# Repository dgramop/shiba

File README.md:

# shiba
An arduino-compatible version of "Pluto", a smartwatch with the same form factor as the F91-W

I abandoned this project after finishing the hardware designs, but I learned a lot from working on it. I learned a lot about KiCAD and EDA stuff in general. I also learned that Arduino is slightly overrated. AVR Microcontrollers are not a one-size fits all, and direct driving an LCD with an MCU doesn't make a whole lot of sense. I had initially planned on direct driving the LCD to save space, but because the MCU I selected did not have a real-time clock, I had to use additional space on the board for an RTC chip that could be configured to interrupt the MCU. This means that there's no space left for other sensors and connectors that could be used to add new features to the watch. I had some ideas involving TOTP and a USB connector to make it act as a U2F device, but power and space constraints make a lot of the features I would want not viable. Maybe later on I'll do a project involving a low-power dumb watch, but it probably won't involve AVR

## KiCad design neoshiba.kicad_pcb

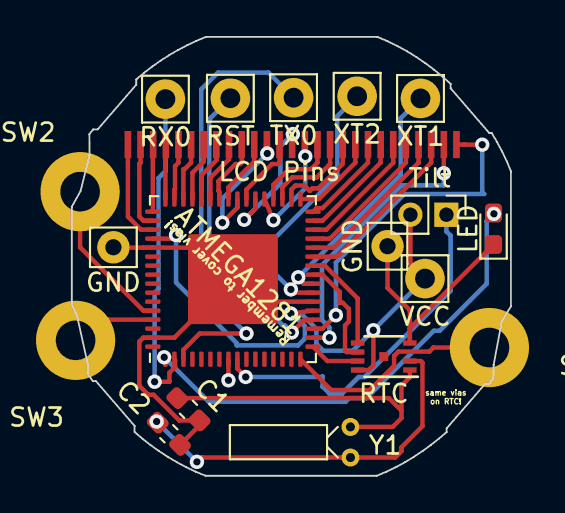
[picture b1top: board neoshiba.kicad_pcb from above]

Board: 2 copper layers, 24.4 x 24.4 mm, 19 parts (0 on the bottom side), 44 nets.

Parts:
ATMEGA1281: ATmega1281V-8MU; QFN-64-1EP_9x9mm_P0.5mm_EP7.65x7.65mm
C1, C2: 15pf; C_0603_1608Metric_Pad1.05x0.95mm_HandSolder
GND: MountingHole_Pad 1.2 or 1mm; Pin_D0.9mm_L10.0mm_W2.4mm_FlatFork
GND#2: MountingHole_Pad, 1.2 or 1mm; Pin_D0.9mm_L10.0mm_W2.4mm_FlatFork
LCD Pins: LCD-F-91W
LED: LED_ALT; LED_0603_1608Metric_Pad1.05x0.95mm_HandSolder
RST: MountingHole_Pad; Pin_D1.1mm_L8.5mm_W2.5mm_FlatFork
RTC: MCP7940N-xSN; DFN-8-1EP_3x2mm_P0.5mm_EP1.3x1.5mm
RX0: MountingHole_Pad; Pin_D1.1mm_L8.5mm_W2.5mm_FlatFork
SW1, SW3: SW_Push; MountingHole_2.2mm_M2_Pad
SW2: SW_Push; MountingHole_2.2mm_M2_Pad-shifted
TX0: MountingHole_Pad; Pin_D1.1mm_L8.5mm_W2.5mm_FlatFork
Tilt: SW_Push; PinHeader_1x02_P2.00mm_Vertical
VCC: MountingHole_Pad; Pin_D1.1mm_L8.5mm_W2.5mm_FlatFork
XT1, XT2: MountingHole_Pad; Pin_D1.1mm_L8.5mm_W2.5mm_FlatFork
Y1: Crystal; Crystal_DS15_D1.5mm_L5.0mm_Horizontal

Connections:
GND: ATMEGA1281.22, ATMEGA1281.53, ATMEGA1281.63, ATMEGA1281.65, C1.1, C2.1, GND.1, GND#2.1, LED.1, RTC.4
unnamed: C1.2, RTC.1, Y1.1
unnamed: C2.2, RTC.2, Y1.2
unnamed: ATMEGA1281.1, LED.2
unnamed: ATMEGA1281.20, RST.1
unnamed: ATMEGA1281.24, XT1.1
unnamed: ATMEGA1281.23, XT2.1
unnamed: ATMEGA1281.2, RX0.1
unnamed: ATMEGA1281.3, TX0.1
unnamed: ATMEGA1281.16, SW1.1
unnamed: ATMEGA1281.60, SW2.1
unnamed: ATMEGA1281.61, SW3.1
unnamed: ATMEGA1281.9, Tilt.1
unnamed: ATMEGA1281.17, RTC.7
unnamed: ATMEGA1281.18, LCD Pins.26
unnamed: ATMEGA1281.19, LCD Pins.27
unnamed: ATMEGA1281.25, RTC.6
unnamed: ATMEGA1281.26, RTC.5
unnamed: ATMEGA1281.27, LCD Pins.25
unnamed: ATMEGA1281.28, LCD Pins.24
unnamed: ATMEGA1281.29, LCD Pins.23
unnamed: ATMEGA1281.30, LCD Pins.22
unnamed: ATMEGA1281.31, LCD Pins.21
unnamed: ATMEGA1281.32, LCD Pins.20
unnamed: ATMEGA1281.33, LCD Pins.19
unnamed: ATMEGA1281.34, LCD Pins.18
unnamed: ATMEGA1281.35, LCD Pins.17
unnamed: ATMEGA1281.36, LCD Pins.16
unnamed: ATMEGA1281.37, LCD Pins.15
unnamed: ATMEGA1281.38, LCD Pins.14
unnamed: ATMEGA1281.39, LCD Pins.13
unnamed: ATMEGA1281.40, LCD Pins.12
unnamed: ATMEGA1281.41, LCD Pins.11
unnamed: ATMEGA1281.42, LCD Pins.10
unnamed: ATMEGA1281.43, LCD Pins.9
unnamed: ATMEGA1281.44, LCD Pins.8
unnamed: ATMEGA1281.45, LCD Pins.7
unnamed: ATMEGA1281.46, LCD Pins.6
unnamed: ATMEGA1281.47, LCD Pins.5
unnamed: ATMEGA1281.48, LCD Pins.4
unnamed: ATMEGA1281.49, LCD Pins.3
unnamed: ATMEGA1281.50, LCD Pins.2
unnamed: ATMEGA1281.51, LCD Pins.1
VCC: ATMEGA1281.21, ATMEGA1281.52, RTC.8, Tilt.2, VCC.1

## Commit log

2019-01-31 Added license
2019-01-31 Upload files to ''
2019-01-31 Update 'README.md'
